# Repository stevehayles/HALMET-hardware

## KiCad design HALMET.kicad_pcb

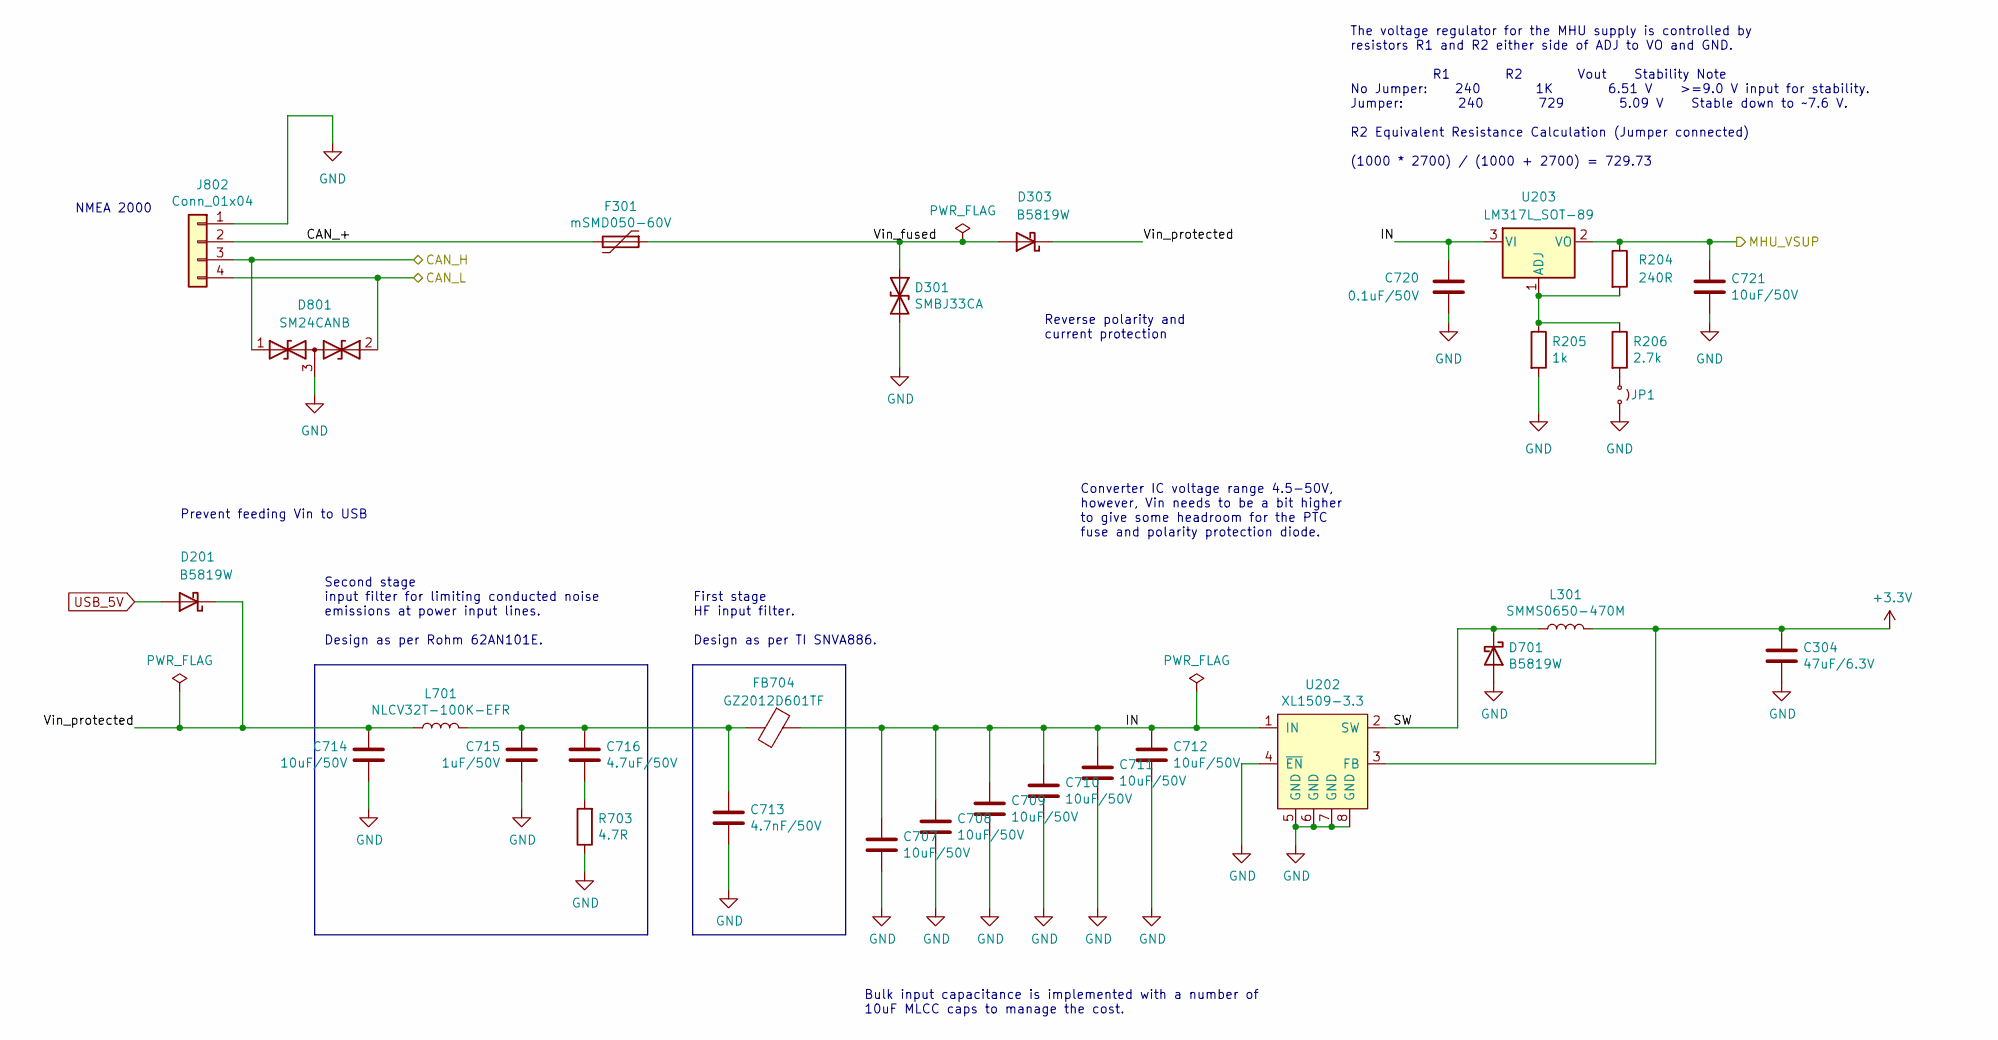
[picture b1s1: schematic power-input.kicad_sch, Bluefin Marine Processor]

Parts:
C304: 47uF/6.3V; C_1206_3216Metric; LCSC C96123
C707, C708, C709, C710, C711, C712, C714, C721: 10uF/50V; C_1206_3216Metric; LCSC C13585
C713: 4.7nF/50V; C_0402_1005Metric; LCSC C1538
C715: 1uF/50V; C_0805_2012Metric; LCSC C28323
C716: 4.7uF/50V; C_1206_3216Metric; LCSC C29823
C720: 0.1uF/50V; C_1206_3216Metric; LCSC C24497
D201, D303, D701: B5819W; D_SOD-123; LCSC C8598
D301: SMBJ33CA; D_SMB; LCSC C114000
D801: SM24CANB; SOT-23; LCSC C41376477
F301: mSMD050-60V; Fuse_1812_4532Metric; LCSC C70113
FB704: GZ2012D601TF; L_0805_2012Metric; LCSC C1017
J802: Conn_01x04; PhoenixContact_MCV_1,5_4-G-3.81_1x04_P3.81mm_Vertical; LCSC C8410
JP1: Jumper_2_Small_Open; PinHeader_1x02_P2.00mm_Vertical; LCSC C541856
L301: SMMS0650-470M; SMMS0650-1R0M; LCSC C149588
L701: NLCV32T-100K-EFR; L_1210_3225Metric; LCSC C295195
R204: 240R; R_0402_1005Metric; LCSC C25094
R205: 1k; R_0402_1005Metric; LCSC C11702
R206: 2.7k; R_0402_1005Metric; LCSC C25885
R703: 4.7R; R_0603_1608Metric; LCSC C23164
U202: XL1509-3.3; SOP-8_3.9x4.9mm_P1.27mm; LCSC C2681226
U203: LM317L_SOT-89; SOT-89-3; LCSC C5444280

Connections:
+3.3V: C304.1, L301.2, U202.3 (FB); also elsewhere on the board
/CAN_H: D801.1 (A1), J802.3; also elsewhere on the board
/CAN_L: D801.2 (A2), J802.4; also elsewhere on the board
/MHU_VSUP: C721.1, R204.1, U203.2 (VO); also elsewhere on the board
/Power input/CAN_+: F301.2, J802.2
/Power input/IN: C707.1, C708.1, C709.1, C710.1, C711.1, C712.1, C720.1, FB704.1, U202.1 (IN), U203.3 (VI)
/Power input/SW: D701.1 (K), L301.1, U202.2 (SW)
/Power input/Vin_fused: D301.1 (A1), D303.2 (A), F301.1
/Power input/Vin_protected: C714.2, D201.1 (K), D303.1 (K), L701.1
GND: C304.2, C707.2, C708.2, C709.2, C710.2, C711.2, C712.2, C713.2, C714.1, C715.1, C720.2, C721.2, D301.2 (A2), D701.2 (A), D801.3 (common), J802.1, JP1.2 (B), R205.2, R703.1, U202.4 (~EN), U202.5 (GND), U202.6 (GND), U202.7 (GND), U202.8 (GND); also elsewhere on the board
unnamed: C713.1, C715.2, C716.1, FB704.2, L701.2
unnamed: C716.2, R703.2
unnamed: JP1.1 (A), R206.2
unnamed: R204.2, R205.1, R206.1, U203.1 (ADJ)
USB_5V: D201.2 (A); also elsewhere on the board

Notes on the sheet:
Converter IC voltage range 4.5-50V, however, Vin needs to be a bit higher to give some headroom for the PTC fuse and polarity protection diode.
NMEA 2000
Bulk input capacitance is implemented with a number of 10uF MLCC caps to manage the cost.
Second stage input filter for limiting conducted noise emissions at power input lines. Design as per Rohm 62AN101E.
First stage HF input filter. Design as per TI SNVA886.
The voltage regulator for the MHU supply is controlled by resistors R1 and R2 either side of ADJ to VO and GND. R1 R2 Vout Stability Note No Jumper: 240 1K 6.51 V >=9.0 V input for stability. Jumper: 240 729 5.09 V Stable down to ~7.6 V. R2 Equivalent Resistance Calculation (Jumper connected) (1000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
Prevent feeding Vin to USB
Reverse polarity and current protection

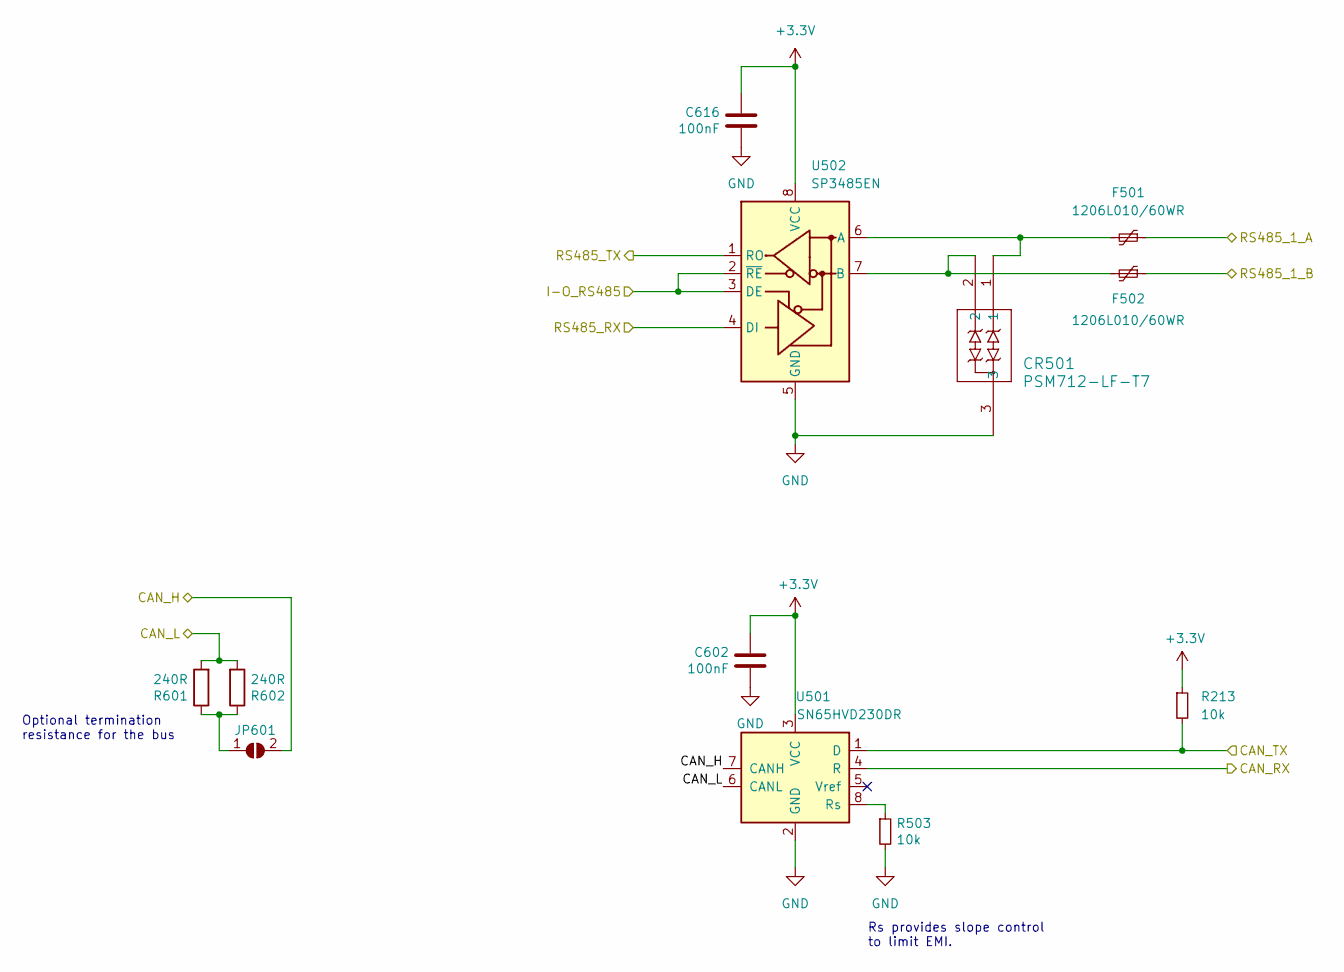
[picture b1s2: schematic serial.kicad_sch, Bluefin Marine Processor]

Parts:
C602, C616: 100nF; C_0402_1005Metric; LCSC C1525
CR501: PSM712-LF-T7; CR_SOT-23_PTD; LCSC C32677
F501, F502: 1206L010/60WR; 1206L075132WR; LCSC C2153714
JP601: SolderJumper_2_Open; SolderJumper-2_P1.3mm_Open_TrianglePad_Narrow
R213, R503: 10k; R_0402_1005Metric; LCSC C25744
R601, R602: 240R; R_0805_2012Metric; LCSC C17572
U501: SN65HVD230DR; SOIC-8_3.9x4.9mm_P1.27mm; LCSC C12084
U502: SP3485EN; SOIC-8_3.9x4.9mm_P1.27mm; LCSC C8963

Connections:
+3.3V: C602.1, C616.1, R213.1, U501.3 (VCC), U502.8 (VCC); also elsewhere on the board
/CAN_H: JP601.2 (B), U501.7 (CANH); also elsewhere on the board
/CAN_L: R601.2, R602.2, U501.6 (CANL); also elsewhere on the board
/CAN_RX: U501.4 (R); also elsewhere on the board
/CAN_TX: R213.2, U501.1 (D); also elsewhere on the board
/I-O_RS485: U502.2 (~RE), U502.3 (DE); also elsewhere on the board
/RS485_1_A: F501.1; also elsewhere on the board
/RS485_1_B: F502.1; also elsewhere on the board
/UART1_RX: U502.1 (RO); also elsewhere on the board
/UART1_TX: U502.4 (DI); also elsewhere on the board
GND: C602.2, C616.2, CR501.3, R503.2, U501.2 (GND), U502.5 (GND); also elsewhere on the board
unnamed: JP601.1 (A), R601.1, R602.1
unnamed: R503.1, U501.8 (Rs)
unnamed: CR501.1, F501.2, U502.6 (A)
unnamed: CR501.2, F502.2, U502.7 (B)

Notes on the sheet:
Rs provides slope control to limit EMI.
Optional termination resistance for the bus

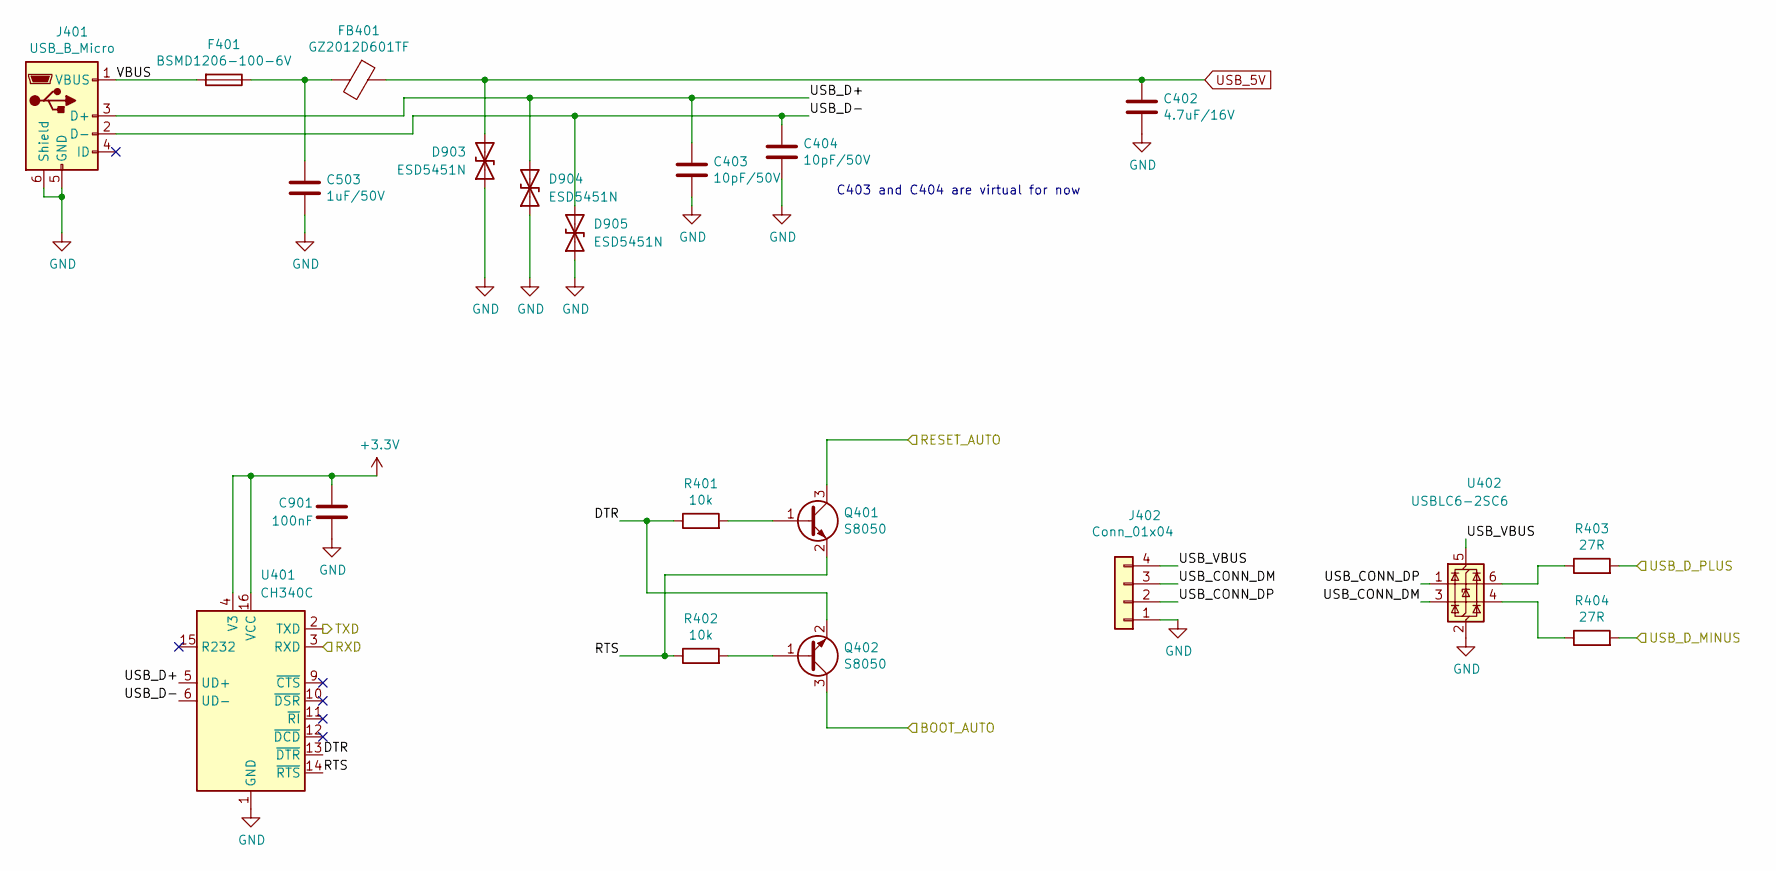
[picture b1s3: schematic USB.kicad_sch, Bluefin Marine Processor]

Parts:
C402: 4.7uF/16V; C_0603_1608Metric; LCSC C19666
C403, C404: 10pF/50V; C_0402_1005Metric; LCSC C32949
C503: 1uF/50V; C_0805_2012Metric; LCSC C28323
C901: 100nF; C_0402_1005Metric; LCSC C1525
D903, D904, D905: ESD5451N; D_0402_1005Metric; LCSC C2936977
F401: BSMD1206-100-6V; Fuse_1206_3216Metric; LCSC C883129
FB401: GZ2012D601TF; L_0805_2012Metric; LCSC C1017
J401: USB_B_Micro; USB_Micro-B_Wuerth_614105150721_Vertical; LCSC C145795
J402: Conn_01x04; JST_SH_BM04B-SRSS-TB_1x04-1MP_P1.00mm_Vertical; LCSC C160390
Q401, Q402: S8050; SOT-23; LCSC C2146
R401, R402: 10k; R_0402_1005Metric; LCSC C25744
R403, R404: 27R; R_0201_0603Metric; LCSC C270320
U401: CH340C; SOIC-16_3.9x9.9mm_P1.27mm; LCSC C84681
U402: USBLC6-2SC6; SOT-23-6; LCSC C7519

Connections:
+3.3V: C901.1, U401.4 (V3), U401.16 (VCC); also elsewhere on the board
/BOOT_AUTO: Q402.3 (C); also elsewhere on the board
/RESET_AUTO: Q401.3 (C); also elsewhere on the board
/UART0_RX: U401.2 (TXD); also elsewhere on the board
/UART0_TX: U401.3 (RXD); also elsewhere on the board
/USB/DTR: Q402.2 (E), R401.1, U401.13 (~DTR)
/USB/RTS: Q401.2 (E), R402.1, U401.14 (~RTS)
/USB/USB_CONN_DM: J402.3, U402.3 (I/O2)
/USB/USB_CONN_DP: J402.2, U402.1 (I/O1)
/USB/USB_D+: C403.1, D904.2 (A2), J401.3 (D+), U401.5 (UD+)
/USB/USB_D-: C404.1, D905.2 (A2), J401.2 (D-), U401.6 (UD-)
/USB/USB_VBUS: J402.4, U402.5 (VBUS)
/USB/VBUS: F401.2, J401.1 (VBUS)
/USB_D_MINUS: R404.2; also elsewhere on the board
/USB_D_PLUS: R403.2; also elsewhere on the board
GND: C402.2, C403.2, C404.2, C503.2, C901.2, D903.1 (A1), D904.1 (A1), D905.1 (A1), J401.5 (GND), J401.6 (Shield), J402.1, U401.1 (GND), U402.2 (GND); also elsewhere on the board
unnamed: C503.1, F401.1, FB401.2
unnamed: Q401.1 (B), R401.2
unnamed: Q402.1 (B), R402.2
unnamed: R403.1, U402.6 (I/O1)
unnamed: R404.1, U402.4 (I/O2)
USB_5V: C402.1, D903.2 (A2), FB401.1; also elsewhere on the board

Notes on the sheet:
C403 and C404 are virtual for now

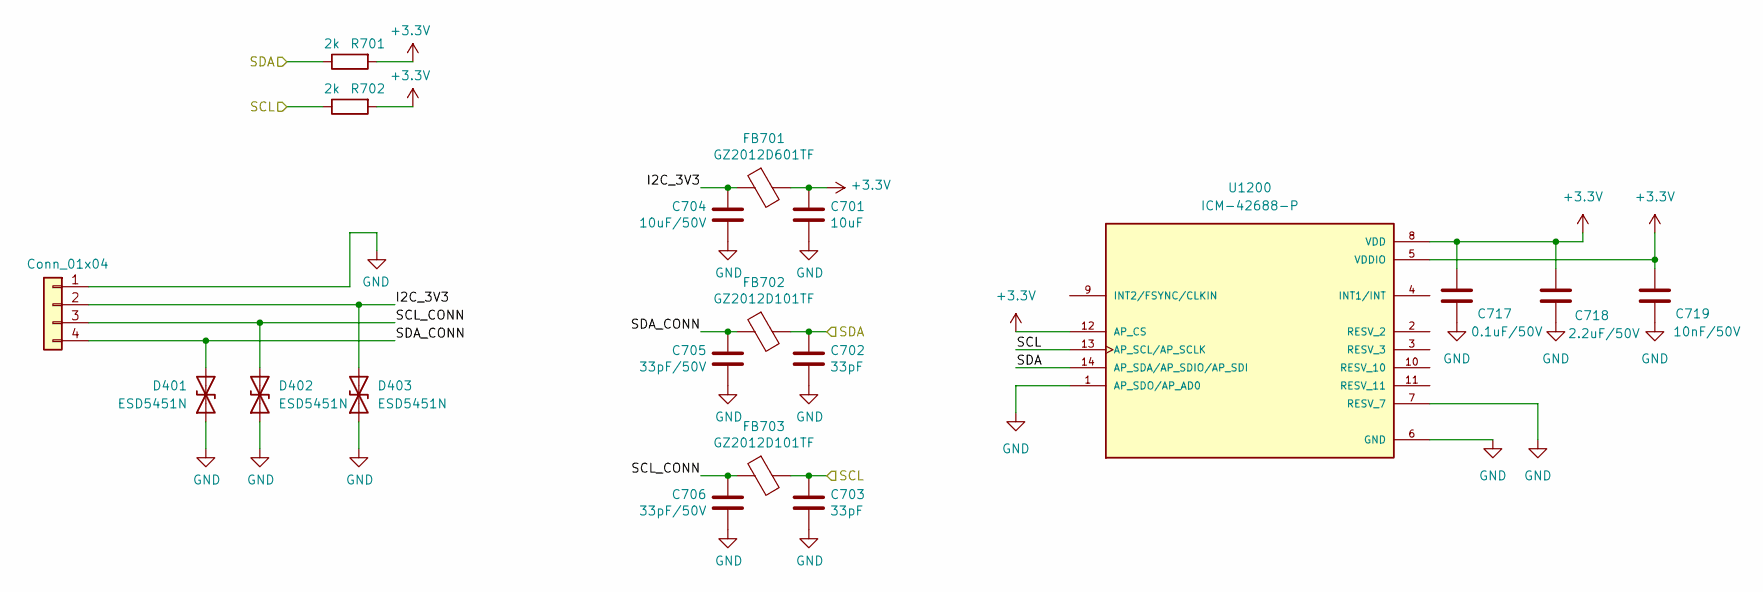
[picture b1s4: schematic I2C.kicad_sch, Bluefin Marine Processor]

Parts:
C701: 10uF; C_0402_1005Metric; LCSC C15525
C702, C703: 33pF; C_0402_1005Metric; LCSC C1562
C704: 10uF/50V; C_1206_3216Metric; LCSC C13585
C705, C706: 33pF/50V; C_0603_1608Metric; LCSC C1663
C717: 0.1uF/50V; C_1206_3216Metric; LCSC C24497
C718: 2.2uF/50V; C_1206_3216Metric; LCSC C50254
C719: 10nF/50V; C_1206_3216Metric; LCSC C153292
D401, D402, D403: ESD5451N; D_0402_1005Metric; LCSC C2936977
FB701: GZ2012D601TF; L_0805_2012Metric; LCSC C1017
FB702, FB703: GZ2012D101TF; L_0805_2012Metric; LCSC C1015
J702: Conn_01x04; PinSocket_1x04_P2.54mm_Vertical; LCSC C124413
R701, R702: 2k; R_0402_1005Metric; LCSC C4109
U1200: ICM-42688-P; PQFN50P300X250X97-14N; PARTREV 1.2; LCSC C1850418

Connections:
+3.3V: C701.1, C717.1, C718.1, C719.1, FB701.2, R701.2, R702.2, U1200.5 (VDDIO), U1200.8 (VDD), U1200.12 (AP_CS); also elsewhere on the board
/I2C/I2C_3V3: C704.1, D403.2 (A2), FB701.1, J702.2
/I2C/SCL_CONN: C706.1, D402.2 (A2), FB703.1, J702.3
/I2C/SDA_CONN: C705.1, D401.2 (A2), FB702.1, J702.4
/SCL: C703.1, FB703.2, R702.1, U1200.13 (AP_SCL/AP_SCLK); also elsewhere on the board
/SDA: C702.1, FB702.2, R701.1, U1200.14 (AP_SDA/AP_SDIO/AP_SDI); also elsewhere on the board
GND: C701.2, C702.2, C703.2, C704.2, C705.2, C706.2, C717.2, C718.2, C719.2, D401.1 (A1), D402.1 (A1), D403.1 (A1), J702.1, U1200.1 (AP_SDO/AP_AD0), U1200.6 (GND), U1200.7 (RESV_7); also elsewhere on the board

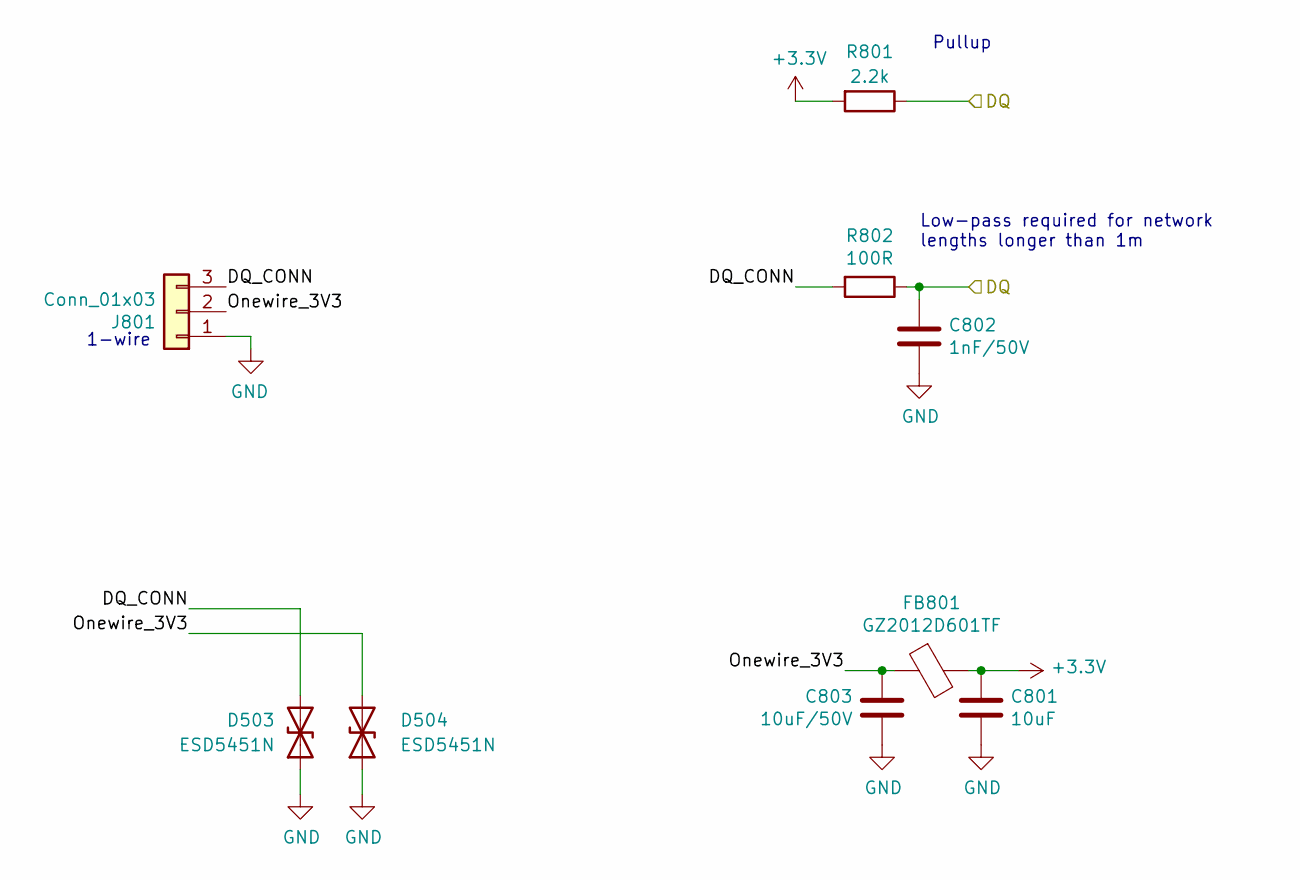
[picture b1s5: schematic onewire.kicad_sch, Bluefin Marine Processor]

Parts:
C801: 10uF; C_0402_1005Metric; LCSC C15525
C802: 1nF/50V; C_0603_1608Metric; LCSC C1588
C803: 10uF/50V; C_1206_3216Metric; LCSC C13585
D503, D504: ESD5451N; D_0402_1005Metric; LCSC C2936977
FB801: GZ2012D601TF; L_0805_2012Metric; LCSC C1017
J801: Conn_01x03; PinHeader_1x03_P2.54mm_Vertical; LCSC C49257
R801: 2.2k; R_0402_1005Metric; LCSC C25879
R802: 100R; R_0805_2012Metric; LCSC C17408

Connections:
+3.3V: C801.1, FB801.2, R801.2; also elsewhere on the board
/DQ: C802.1, R801.1, R802.1; also elsewhere on the board
/Onewire/DQ_CONN: D503.2 (A2), J801.3, R802.2
/Onewire/Onewire_3V3: C803.1, D504.2 (A2), FB801.1, J801.2
GND: C801.2, C802.2, C803.2, D503.1 (A1), D504.1 (A1), J801.1; also elsewhere on the board

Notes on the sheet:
1-wire
Low-pass required for network lengths longer than 1m
Pullup

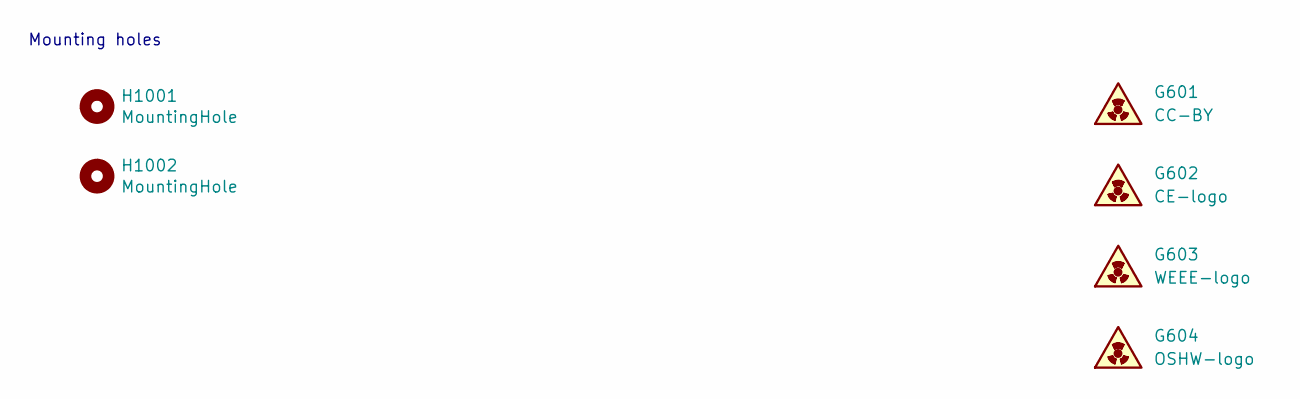
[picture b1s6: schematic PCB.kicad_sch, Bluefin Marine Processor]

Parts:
G601: CC-BY; cc-by_5mm
G602: CE-logo; CE-Logo_11.2x8mm_SilkScreen
G603: WEEE-logo; WEEE-Logo_5.6x8mm_SilkScreen
G604: OSHW-logo; OSHW-Logo2_9.8x8mm_SilkScreen
H1001, H1002: MountingHole; MountingSlot_3.2mm_M3_Unplated

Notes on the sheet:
Mounting holes

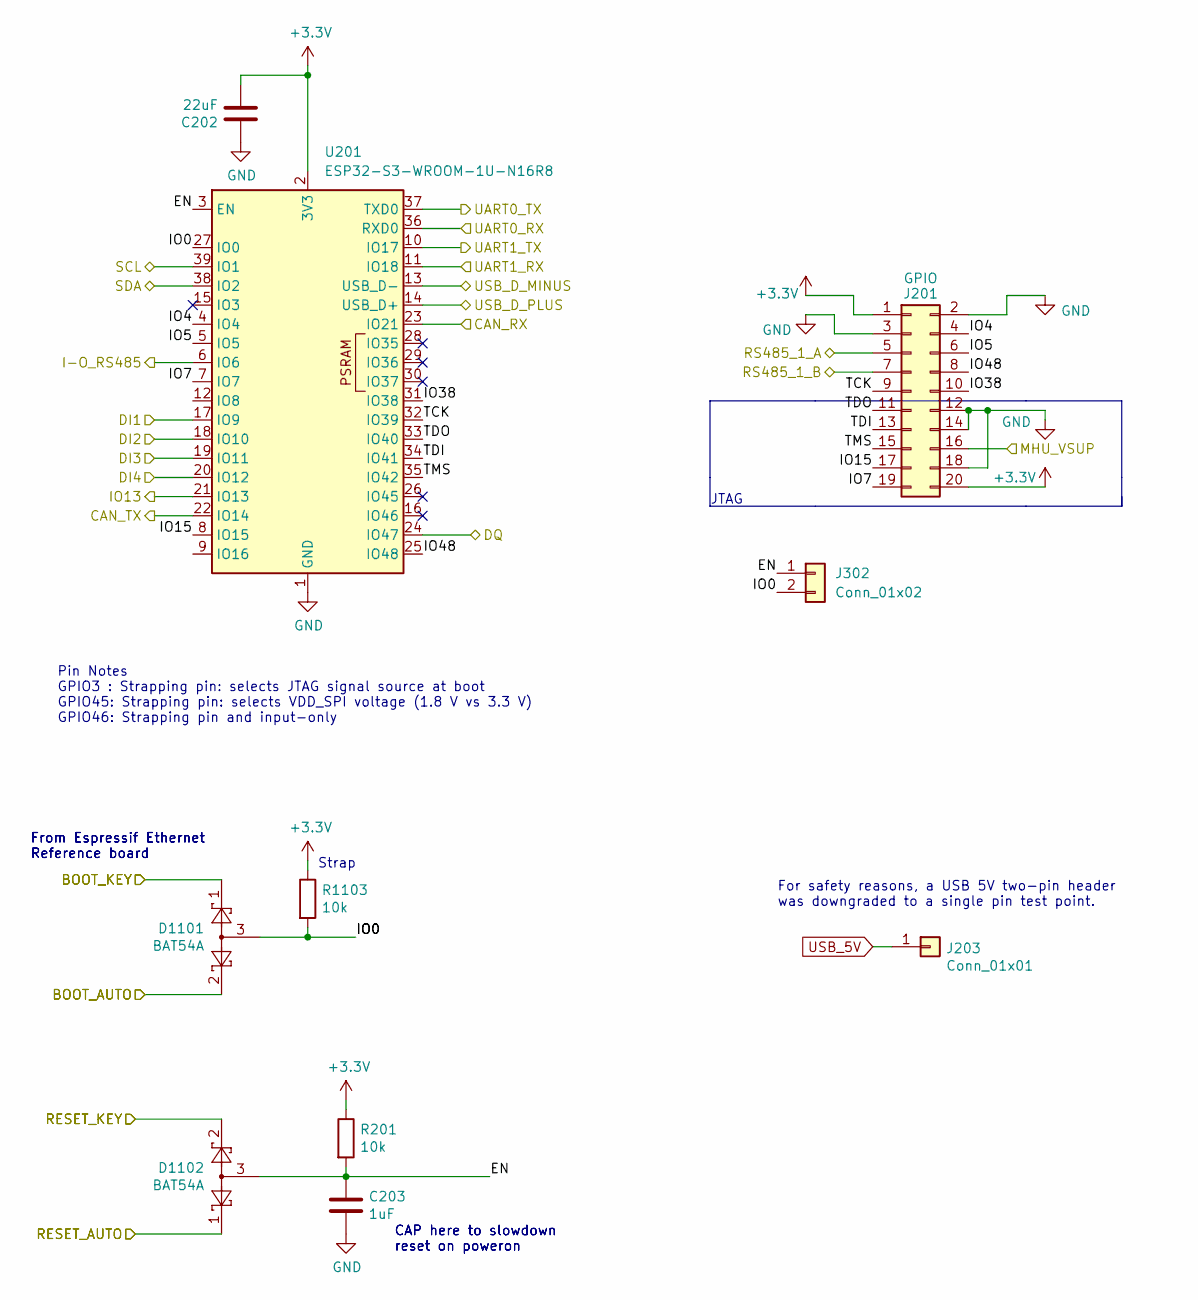
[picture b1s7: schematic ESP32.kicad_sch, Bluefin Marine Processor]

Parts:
C202: 22uF; C_0603_1608Metric; LCSC C59461
C203: 1uF; C_0402_1005Metric; LCSC C52923
D1101, D1102: BAT54A; SOT-323_SC-70; LCSC C78261
J201: GPIO; PinHeader_2x10_P2.54mm_Vertical; LCSC C492427
J203: Conn_01x01; TestPoint_Pad_D2.0mm
J302: Conn_01x02; PinHeader_1x02_P2.54mm_Vertical
R201, R1103: 10k; R_0402_1005Metric; LCSC C25744
U201: ESP32-S3-WROOM-1U-N16R8; ESP32-S3-WROOM-1U; LCSC C3013946

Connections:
+3.3V: C202.2, J201.1, J201.20, R201.1, R1103.1, U201.2 (3V3); also elsewhere on the board
/BOOT_AUTO: D1101.2; also elsewhere on the board
/BOOT_KEY: D1101.1; also elsewhere on the board
/CAN_RX: U201.23 (IO21); also elsewhere on the board
/CAN_TX: U201.22 (IO14); also elsewhere on the board
/DI1: U201.17 (IO9); also elsewhere on the board
/DI2: U201.18 (IO10); also elsewhere on the board
/DI3: U201.19 (IO11); also elsewhere on the board
/DI4: U201.20 (IO12); also elsewhere on the board
/DQ: U201.24 (IO47); also elsewhere on the board
/ESP32/EN: C203.1, D1102.3, J302.1, R201.2, U201.3 (EN)
/ESP32/IO0: D1101.3, J302.2, R1103.2, U201.27 (IO0)
/ESP32/IO4: J201.4, U201.4 (IO4)
/ESP32/IO5: J201.6, U201.5 (IO5)
/ESP32/IO7: J201.19, U201.7 (IO7)
/ESP32/IO15: J201.17, U201.8 (IO15)
/ESP32/IO38: J201.10, U201.31 (IO38)
/ESP32/IO48: J201.8, U201.25 (IO48)
/ESP32/TCK: J201.9, U201.32 (IO39)
/ESP32/TDI: J201.13, U201.34 (IO41)
/ESP32/TDO: J201.11, U201.33 (IO40)
/ESP32/TMS: J201.15, U201.35 (IO42)
/I-O_RS485: U201.6 (IO6); also elsewhere on the board
/LED: U201.21 (IO13); also elsewhere on the board
/MHU_VSUP: J201.16; also elsewhere on the board
/RESET_AUTO: D1102.1; also elsewhere on the board
/RESET_KEY: D1102.2; also elsewhere on the board
/RS485_1_A: J201.5; also elsewhere on the board
/RS485_1_B: J201.7; also elsewhere on the board
/SCL: U201.39 (IO1); also elsewhere on the board
/SDA: U201.38 (IO2); also elsewhere on the board
/UART0_RX: U201.36 (RXD0); also elsewhere on the board
/UART0_TX: U201.37 (TXD0); also elsewhere on the board
/UART1_RX: U201.11 (IO18); also elsewhere on the board
/UART1_TX: U201.10 (IO17); also elsewhere on the board
/USB_D_MINUS: U201.13 (USB_D-); also elsewhere on the board
/USB_D_PLUS: U201.14 (USB_D+); also elsewhere on the board
GND: C202.1, C203.2, J201.2, J201.3, J201.12, J201.14, J201.18, U201.1 (GND), U201.40 (GND), U201.41 (GND); also elsewhere on the board
USB_5V: J203.1; also elsewhere on the board

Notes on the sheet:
CAP here to slowdown reset on poweron
JTAG
From Espressif Ethernet Reference board
Strap
Pin Notes GPIO3 : Strapping pin: selects JTAG signal source at boot GPIO45: Strapping pin: selects VDD_SPI voltage (1.8 V vs 3.3 V) GPIO46: Strapping pin and input-only
For safety reasons, a USB 5V two-pin header was downgraded to a single pin test point.

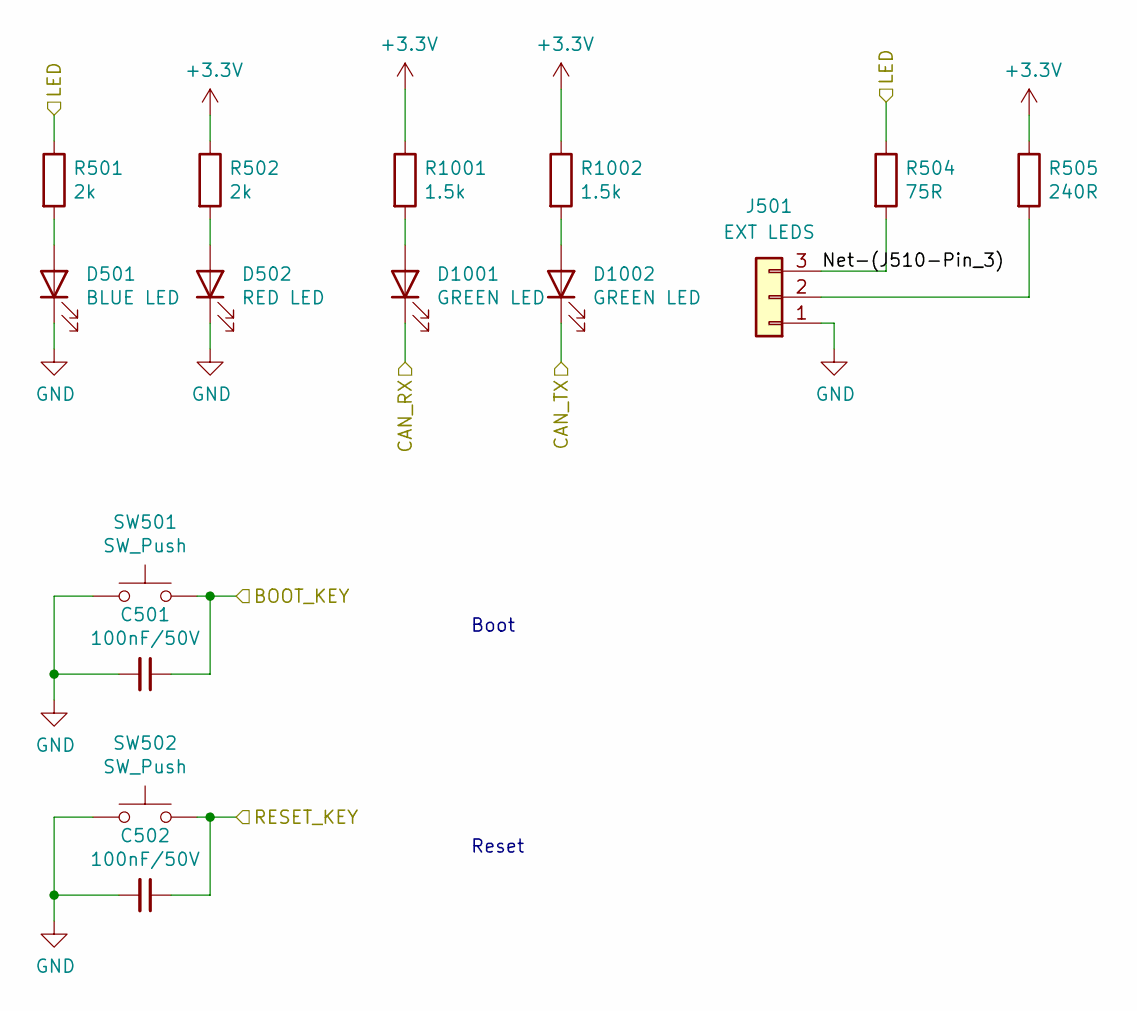
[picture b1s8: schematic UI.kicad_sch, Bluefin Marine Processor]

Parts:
C501, C502: 100nF/50V; C_0603_1608Metric; LCSC C14663
D501: BLUE LED; LED_0603_1608Metric; LCSC C84266
D502: RED LED; LED_0603_1608Metric; LCSC C2286
D1001, D1002: GREEN LED; LED_0603_1608Metric; LCSC C965804
J501: EXT LEDS; PinHeader_1x03_P2.00mm_Vertical; LCSC C541857
R501, R502: 2k; R_0402_1005Metric; LCSC C4109
R504: 75R; R_0402_1005Metric; LCSC C25133
R505: 240R; R_0402_1005Metric; LCSC C25094
R1001, R1002: 1.5k; R_0402_1005Metric; LCSC C25867
SW501, SW502: SW_Push; SW_SPST_TL3342; LCSC C318887

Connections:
+3.3V: R502.1, R505.1, R1001.1, R1002.1; also elsewhere on the board
/BOOT_KEY: C501.1, SW501.2; also elsewhere on the board
/CAN_RX: D1001.1 (K); also elsewhere on the board
/CAN_TX: D1002.1 (K); also elsewhere on the board
/LED: R501.1, R504.1; also elsewhere on the board
/RESET_KEY: C502.1, SW502.2; also elsewhere on the board
/User Interface/<NO NET>: J501.3, R504.2
GND: C501.2, C502.2, D501.1 (K), D502.1 (K), J501.1, SW501.1, SW502.1; also elsewhere on the board
unnamed: D501.2 (A), R501.2
unnamed: D502.2 (A), R502.2
unnamed: D1001.2 (A), R1001.2
unnamed: D1002.2 (A), R1002.2
unnamed: J501.2, R505.2

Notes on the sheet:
Reset
Boot

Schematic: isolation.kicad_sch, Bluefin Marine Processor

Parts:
C1201, C1202, C1208, C1210: 4.7uF; C_0402_1005Metric; LCSC C23733
C1203: 10uF/10V; C_0603_1608Metric; LCSC C19702
C1204, C1205, C1206, C1207: 100nF; C_0402_1005Metric; LCSC C1525
C1209: 220pF/2kV; C_1808_4520Metric; LCSC C2940747
J1201: Conn_01x02; PinHeader_1x02_P2.54mm_Vertical
L1201, L1202: CMH201209B4R7MT; L_0805_2012Metric; LCSC C394959
PS1201: B0305S-1WR3; Converter_DCDC_Murata_MEE1SxxxxSC_THT; LCSC C7465186
R1201: 330R; R_0402_1005Metric; LCSC C25104
R1202, R1203: 2k; R_0402_1005Metric; LCSC C4109
U1201: π140U30; SOIC-16_4.55x10.3mm_P1.27mm; LCSC C910134
U1202: ISO1540; SOIC-8_3.9x4.9mm_P1.27mm; LCSC C179739
U1203: XC6206P332MR; SOT-23-3; LCSC C5446

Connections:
+3.3V: C1201.1, C1206.1, C1207.1, L1201.1, U1201.16 (VDD2), U1202.1 (VCC1); also elsewhere on the board
+3.3V_1: C1203.1, C1204.1, C1205.1, J1201.2, R1201.1, R1202.2, R1203.2, U1201.1 (VDD1), U1202.8 (VCC2), U1203.2 (VOUT); also elsewhere on the board
/Analog input/SCL: R1203.1, U1202.6 (SCL2); also elsewhere on the board
/Analog input/SDA: R1202.1, U1202.7 (SDA2); also elsewhere on the board
/DI1: U1201.14 (VOA); also elsewhere on the board
/DI2: U1201.13 (VOB); also elsewhere on the board
/DI3: U1201.12 (VOC); also elsewhere on the board
/DI4: U1201.11 (VOD); also elsewhere on the board
/Digital input/DigIn1: U1201.3 (VIA); also elsewhere on the board
/Digital input/DigIn2: U1201.4 (VIB); also elsewhere on the board
/Digital input/DigIn3: U1201.5 (VIC); also elsewhere on the board
/Digital input/DigIn4: U1201.6 (VID); also elsewhere on the board
/Isolation barrier/5V_unreg: C1202.1, L1202.2, U1203.3 (VIN)
/Isolation barrier/Vin_: C1208.1, L1201.2, PS1201.2 (+Vin)
/Isolation barrier/Vout_: C1210.1, L1202.1, PS1201.4 (+Vout)
/SCL: U1202.3 (SCL1); also elsewhere on the board
/SDA: U1202.2 (SDA1); also elsewhere on the board
GND: C1201.2, C1206.2, C1207.2, C1208.2, C1209.1, PS1201.1 (-Vin), U1201.9 (GND2), U1201.15 (GND2), U1202.4 (GND1); also elsewhere on the board
GND1: C1202.2, C1203.2, C1204.2, C1205.2, C1209.2, C1210.2, J1201.1, PS1201.3 (-Vout), R1201.2, U1201.2 (GND1), U1201.8 (GND1), U1202.5 (GND2), U1203.1 (GND); also elsewhere on the board

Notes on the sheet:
Dummy load to help with load regulation
Isolation barrier

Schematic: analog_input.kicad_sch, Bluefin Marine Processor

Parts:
C601, C604, C612, C614: 33pF/50V; C_0603_1608Metric; LCSC C1663
C603, C605, C613, C615: 33pF; C_0402_1005Metric; LCSC C1562
C606, C607, C608, C609, C610, C624: 100nF; C_0402_1005Metric; LCSC C1525
C611: 68nF; C_0603_1608Metric; LCSC C31658
C620, C621, C622, C623: 10nF; C_0402_1005Metric; LCSC C15195
D603, D604, D605, D611: BAT54S; SOT-323_SC-70; LCSC C12741
FB601, FB602, FB603, FB604: GZ2012D101TF; L_0805_2012Metric; LCSC C1015
J602: Conn_02x04_Odd_Even; PinHeader_2x04_P2.54mm_Vertical; LCSC C124386
J604, J605, J606, J607: Conn_01x02; PhoenixContact_MCV_1,5_2-G-3.81_1x02_P3.81mm_Vertical; LCSC C8396
JP602, JP604, JP605: Open; SolderJumper-2_P1.3mm_Open_Pad1.0x1.5mm
JP603: Bridged; SolderJumper-2_P1.3mm_Bridged2Bar_RoundedPad1.0x1.5mm
Q601, Q602, Q603, Q604: BC856BW,115; SOT-323_SC-70; LCSC C28063
R603, R604, R605, R606, R611: 1k; R_0402_1005Metric; LCSC C11702
R607, R608, R609, R610: 30; R_0603_1608Metric; LCSC C22985
R612: 10k; R_0402_1005Metric; LCSC C25744
R613, R614, R616, R618: 20k; R_0603_1608Metric; LCSC C4184
R615, R617, R619, R621: 2.2k; R_0402_1005Metric; LCSC C25879
U601: LMV324; SOIC-14_3.9x8.7mm_P1.27mm; LCSC C362275
U602: ADS1115IDGS; TSSOP-10_3x3mm_P0.5mm; LCSC C37593

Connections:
+3.3V_1: C606.2, C607.2, C608.2, C609.2, C610.1, C624.1, D603.2 (K), D604.2 (K), D605.2 (K), D611.2 (K), JP602.2 (B), R607.1, R608.1, R609.1, R610.1, R611.1, U601.4 (V+), U602.8 (VDD); also elsewhere on the board
/Analog input/ADC_A1: C620.1, D611.3 (COM), R613.1, R621.2, U602.4 (AIN0)
/Analog input/ADC_A2: C621.1, D603.3 (COM), R614.1, R615.2, U602.5 (AIN1)
/Analog input/ADC_A3: C622.1, D604.3 (COM), R616.1, R617.2, U602.6 (AIN2)
/Analog input/ADC_A4: C623.1, D605.3 (COM), R618.1, R619.2, U602.7 (AIN3)
/Analog input/ADDR: JP602.1 (A), JP603.1 (A), JP604.1 (A), JP605.1 (A), U602.1 (ADDR)
/Analog input/INA1: C601.1, FB601.1, J606.2
/Analog input/INA2: C604.1, FB602.1, J604.2
/Analog input/INA3: C612.1, FB603.1, J605.2
/Analog input/INA4: C614.1, FB604.1, J607.2
/Analog input/INFA1: C603.1, FB601.2, J602.2, R613.2
/Analog input/INFA2: C605.1, FB602.2, J602.4, R614.2
/Analog input/INFA3: C613.1, FB603.2, J602.6, R616.2
/Analog input/INFA4: C615.1, FB604.2, J602.8, R618.2
/Analog input/IoutA1: J602.1, Q601.3 (C)
/Analog input/IoutA2: J602.3, Q602.3 (C)
/Analog input/IoutA3: J602.5, Q603.3 (C)
/Analog input/IoutA4: J602.7, Q604.3 (C)
/Analog input/QBA1: Q601.1 (B), U601.14
/Analog input/QBA2: Q602.1 (B), U601.1
/Analog input/QBA3: Q603.1 (B), U601.8
/Analog input/QBA4: Q604.1 (B), U601.7
/Analog input/SCL: JP603.2 (B), U602.10 (SCL); also elsewhere on the board
/Analog input/SDA: JP604.2 (B), U602.9 (SDA); also elsewhere on the board
/Analog input/Vin: C611.1, R611.2, R612.1, U601.3 (+), U601.5 (+), U601.10 (+), U601.12 (+)
GND1: C601.2, C603.2, C604.2, C605.2, C610.2, C611.2, C612.2, C613.2, C614.2, C615.2, C620.2, C621.2, C622.2, C623.2, C624.2, D603.1 (A), D604.1 (A), D605.1 (A), D611.1 (A), J604.1, J605.1, J606.1, J607.1, JP605.2 (B), R612.2, R615.1, R617.1, R619.1, R621.1, U601.11 (V-), U602.3 (GND); also elsewhere on the board
unnamed: Q601.2 (E), R603.1, R607.2
unnamed: Q602.2 (E), R604.1, R608.2
unnamed: Q603.2 (E), R605.1, R609.2
unnamed: Q604.2 (E), R606.1, R610.2
unnamed: C607.1, R604.2, U601.2 (-)
unnamed: C609.1, R606.2, U601.6 (-)
unnamed: C608.1, R605.2, U601.9 (-)
unnamed: C606.1, R603.2, U601.13 (-)

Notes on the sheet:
Vin = 3.0 V
ADS1115 I2C address selection
0x49
EMI filtering
I = (Vcc - Vin) / R = 10 mA
Constant current source
Voltage divider splitting 33.3V to 3.3V
0x48
Input from tank senders. Max measurable resistance 320 ohms.
0x4a
Reference voltage for current sources
0x4b
LP-filter with cutoff at 160 Hz
Connect headers with a jumper to enable the constant current source (active resistance measurement).
Filter cap to 3.3V to avoid a current swing at startup.

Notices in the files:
ESP32.kicad_sch:
https://creativecommons.org/licenses/by-sa/4.0
Bluefin is licensed under CC BY-SA 4.0
Modifications © 2026 Fiftyone North Ltd.
